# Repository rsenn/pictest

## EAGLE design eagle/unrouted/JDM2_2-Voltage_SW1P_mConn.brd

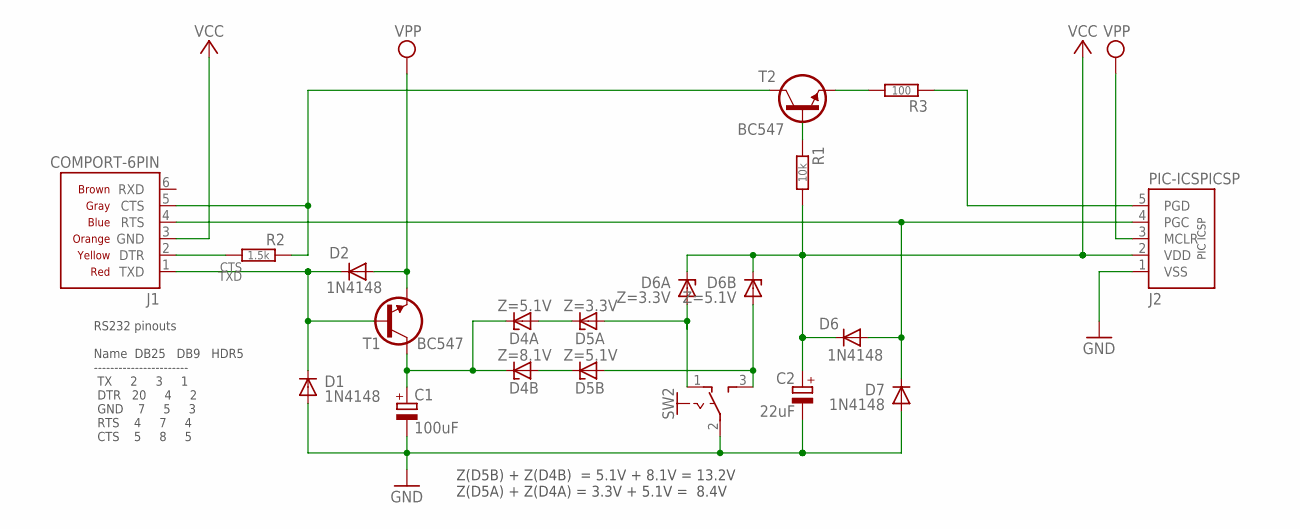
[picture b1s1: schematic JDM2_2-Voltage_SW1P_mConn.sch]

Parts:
C1: 100uF; E2,5-5
C2: 22uF; E2,5-4
D1, D2: 1N4148; DO34-5
D4A: Z=5.1V; DO34Z2,5
D4B: Z=8.1V; DO34Z2,5
D5A: Z=3.3V; DO34Z5
D5B: Z=5.1V; DO34Z5
D6: 1N4148; DO34-5V
D6A: Z=3.3V; DO34Z10V
D6B: Z=5.1V; DO34Z10V
D7: 1N4148; DO34-7V
J1: COMPORT-6PIN; RS232-6PIN
J2: PIC-ICSPICSP; PIC-ICSP
R1: 10k; 0202/7-V
R2: 1.5k; 0202/7-V
R3: 100; 0202/7
SW2: SL-SW-1P-2T-H; SLSW-1P2T-H
T1, T2: BC547; TO92-CBE

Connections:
/MCLR: D2.A, J2.3 (MCLR), T1.E
CLK: D6.A, D7.C, J1.4 (RTS), J2.4 (PGC)
CTS: J1.5 (CTS), R2.1, T2.C
DATA: R3.2, T2.E
GND: C1.-, C2.-, D1.A, D7.A, J2.1 (VSS), SW2.2
unnamed: R1.1, T2.B
unnamed: D5A.A, D6A.A, SW2.1 (O)
unnamed: D5B.A, D6B.A, SW2.3 (S)
unnamed: D4A.A, D5A.C
unnamed: J1.2 (DTR), R2.2
unnamed: D4B.A, D5B.C
PGD: J2.5 (PGD), R3.1
TXD: D1.C, D2.C, J1.1 (TXD), T1.B
VCC: C2.+, D6.C, D6A.C, D6B.C, J1.3 (GND), J2.2 (VDD), R1.2
VPP: C1.+, D4A.C, D4B.C, T1.C

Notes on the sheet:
RS232 pinouts Name DB25 DB9 HDR5 ----------------------- TX 2 3 1 DTR 20 4 2 GND 7 5 3 RTS 4 7 4 CTS 5 8 5
Z(D5B) + Z(D4B) = 5.1V + 8.1V = 13.2V Z(D5A) + Z(D4A) = 3.3V + 5.1V = 8.4V

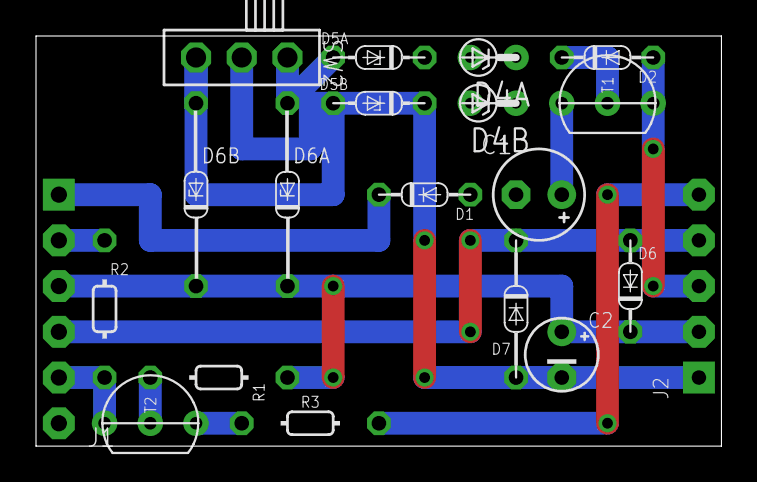
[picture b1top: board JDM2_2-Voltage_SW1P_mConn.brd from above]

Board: 2 copper layers, 38.1 x 22.8 mm, 20 parts (0 on the bottom side), 15 nets.

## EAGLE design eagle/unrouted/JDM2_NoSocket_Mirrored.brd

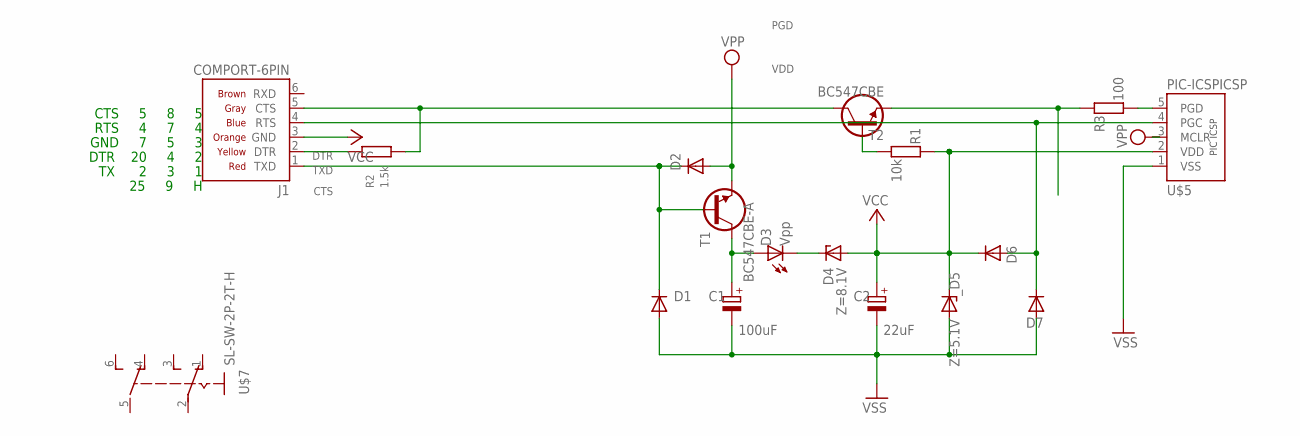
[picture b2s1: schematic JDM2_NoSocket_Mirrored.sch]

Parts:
C1: 100uF; E5-4
C2: 22uF; E2,5-4
D1: 1N4148; DO34-2,5-A
D2, D7: 1N4148; DO34-7
D3: Vpp; LED3MM
D4: Z=8.1V; DO34Z5
D6: 1N4148; DO34-5
J1: COMPORT-6PIN; RS232-6PIN
R1: 10k; 0202/5
R2: 1.5k; 0202/7
R3: 100; 0202/5
T1: BC547CBE-A; TO92-CBE-A
T2: BC547CBE; TO92-CBE
U$5: PIC-ICSPICSP; PIC-ICSP
U$7: SL-SW-2P-2T-H; SLSW-2P2T-H
_D5: Z=5.1V; DO35Z2_54

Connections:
/MCLR: D2.A, T1.E, U$5.3 (MCLR)
CLK: D6.A, D7.C, J1.4 (RTS), U$5.4 (PGC)
CTS: J1.5 (CTS), R2.2, T2.C
DATA: R3.2, T2.E
DTR: J1.2 (DTR), R2.1
unnamed: R1.1, T2.B
unnamed: D3.K (C), D4.C
PGD: R3.1, U$5.5 (PGD)
TXD: D1.C, D2.C, J1.1 (TXD), T1.B
VDD: C2.+, D4.A, D6.C, J1.3 (GND), R1.2, U$5.2 (VDD), _D5.C
VPP: C1.+, D3.A, T1.C
VSS: C1.-, C2.-, D1.A, D7.A, U$5.1 (VSS), _D5.A

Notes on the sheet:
DTR 20 4 2
TX 2 3 1
CTS 5 8 5
GND 7 5 3
RTS 4 7 4
25 9 H

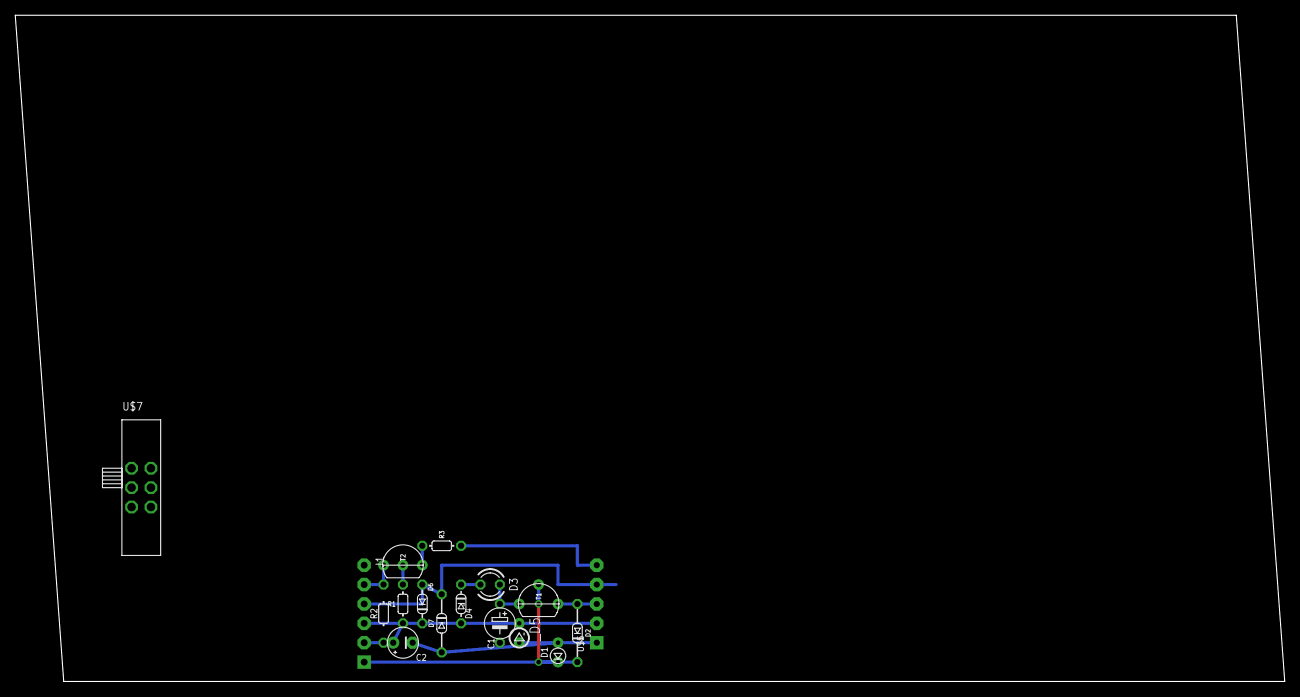
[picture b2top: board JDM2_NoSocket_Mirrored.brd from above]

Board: 2 copper layers, 166.3 x 87.3 mm, 17 parts (0 on the bottom side), 12 nets.

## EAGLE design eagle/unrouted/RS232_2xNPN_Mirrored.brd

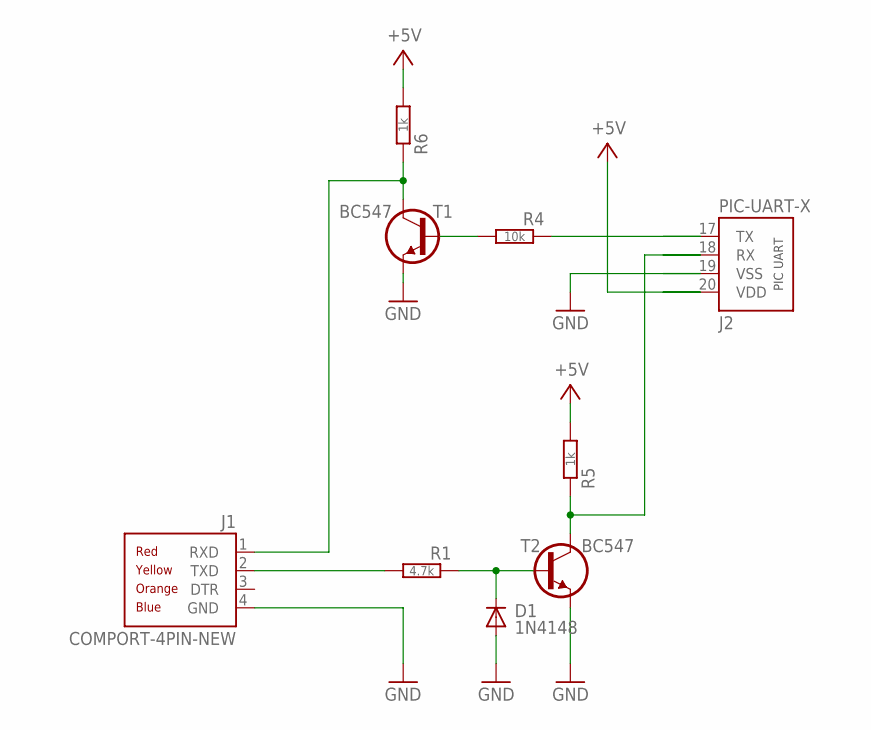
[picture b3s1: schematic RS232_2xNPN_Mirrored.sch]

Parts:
D1: 1N4148; DO34-5
J1: COMPORT-4PIN-NEW; RS232-4PIN-NEW
J2: PIC-UART-X
R1: 4.7k; 0202/7
R4: 10k; 0202/7
R5: 1k; 0202/7-V
R6: 1k; 0202/7
T1, T2: BC547; TO92-CBE

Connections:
+5V: J2.20 (VDD), R5.2, R6.2
GND: D1.A, J1.4 (GND), J2.19 (VSS), T1.E, T2.E
unnamed: J2.18 (RX), R5.1, T2.C
unnamed: D1.C, R1.1, T2.B
unnamed: J1.2 (TXD), R1.2
unnamed: J2.17 (TX), R4.1
unnamed: R4.2, T1.B
unnamed: J1.1 (RXD), R6.1, T1.C

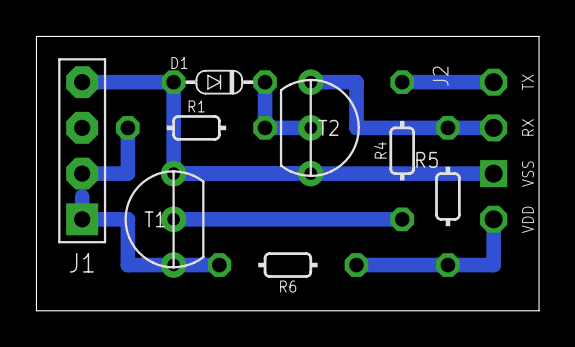
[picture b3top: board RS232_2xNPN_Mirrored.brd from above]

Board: 2 copper layers, 27.9 x 15.2 mm, 9 parts (0 on the bottom side), 8 nets.

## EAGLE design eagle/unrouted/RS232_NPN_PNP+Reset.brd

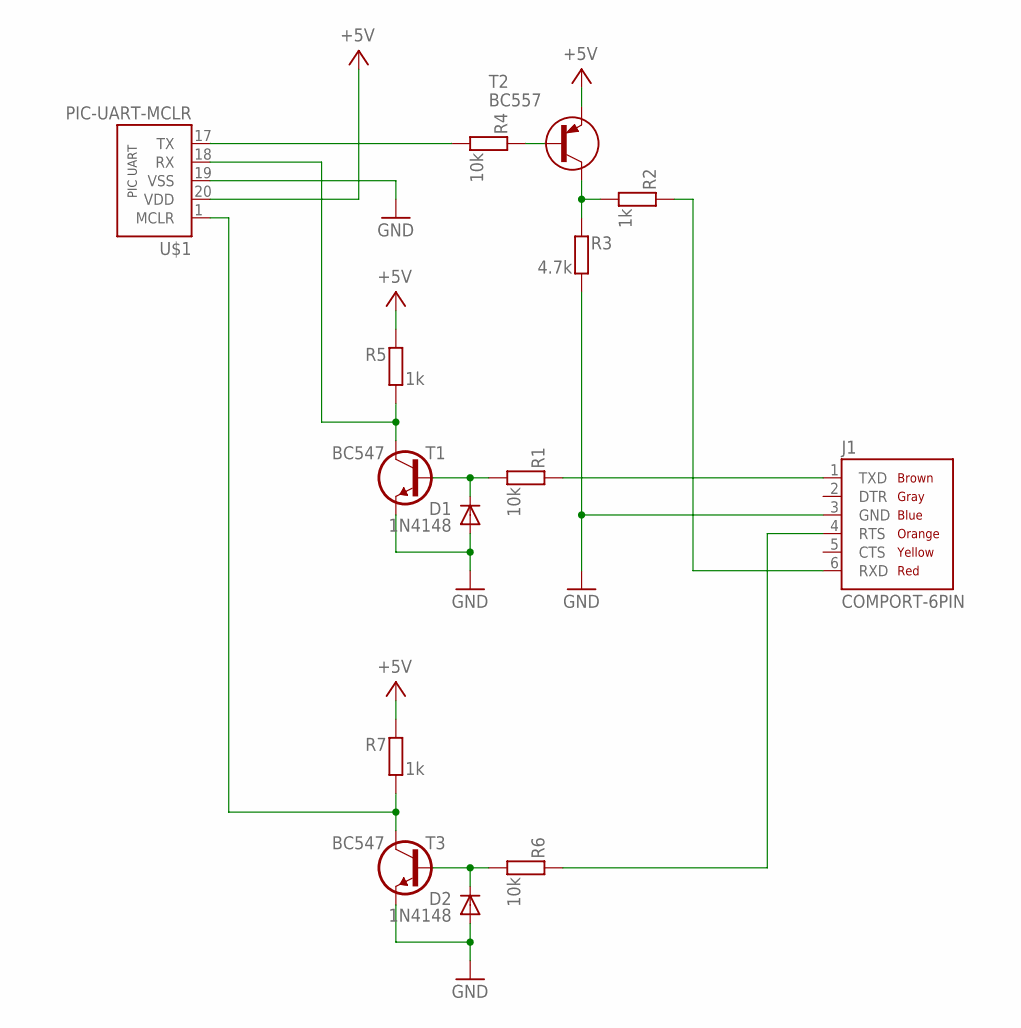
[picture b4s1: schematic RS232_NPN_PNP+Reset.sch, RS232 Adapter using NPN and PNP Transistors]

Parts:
D1, D2: 1N4148; DO34-5
J1: COMPORT-6PIN; RS232-6PIN
R1, R4, R6: 10k; 0202/5
R2, R5: 1k; 0202/5
R3: 4.7k; 0202/5
R7: 1k; 0202/2V
T1, T3: BC547; TO92-CBE
T2: BC557; TO92-CBE
U$1: PIC-UART-MCLR

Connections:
+5V: R5.2, R7.2, T2.E, U$1.20 (VDD)
GND: D1.A, D2.A, J1.3 (GND), R3.1, T1.E, T3.E, U$1.19 (VSS)
unnamed: R5.1, T1.C, U$1.18 (RX)
unnamed: D1.C, R1.1, T1.B
unnamed: J1.1 (TXD), R1.2
unnamed: R4.1, U$1.17 (TX)
unnamed: R4.2, T2.B
unnamed: R2.1, R3.2, T2.C
unnamed: J1.6 (RXD), R2.2
unnamed: R7.1, T3.C, U$1.1 (MCLR)
unnamed: D2.C, R6.1, T3.B
unnamed: J1.4 (RTS), R6.2

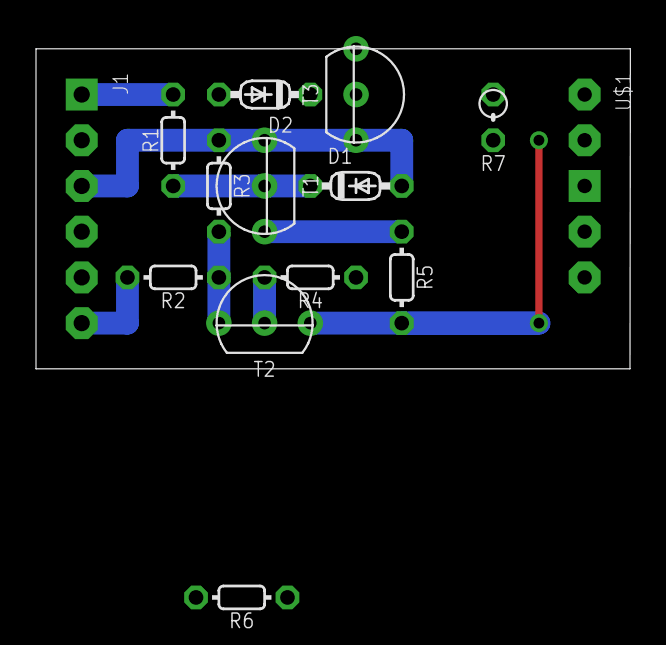
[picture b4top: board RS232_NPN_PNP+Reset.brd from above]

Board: 2 copper layers, 33.0 x 17.8 mm, 14 parts (0 on the bottom side), 12 nets.

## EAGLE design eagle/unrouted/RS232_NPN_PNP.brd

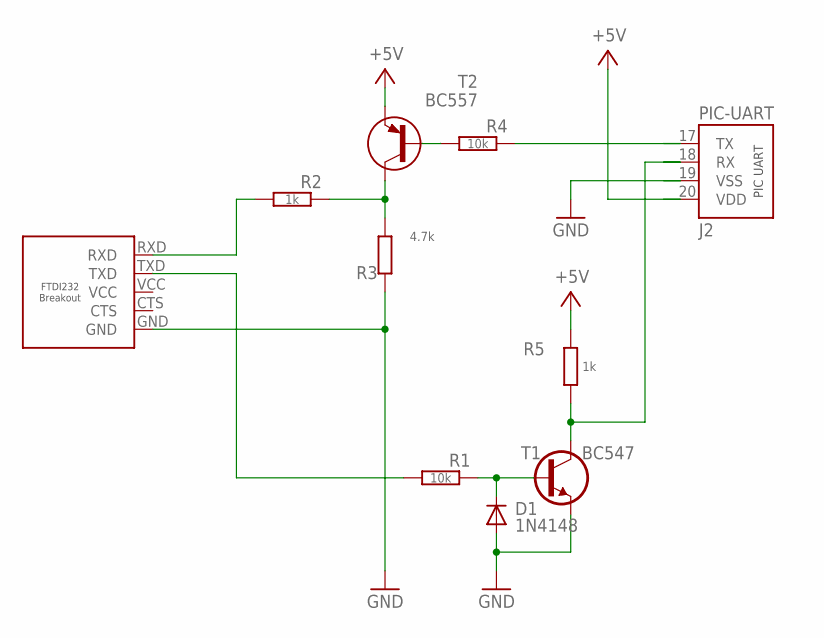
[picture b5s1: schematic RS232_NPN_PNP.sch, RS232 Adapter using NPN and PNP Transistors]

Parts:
D1: 1N4148; DO34-5
J1: FTDI232; FTDI232-BO-5-L
J2: PIC-UART
R1: 10k; 0202/5-V
R2, R5: 1k; 0202/5-V
R3: 4.7k; 0202/5-V
R4: 10k; 0202/5
T1: BC547; TO92-CBE
T2: BC557; TO92-CBE

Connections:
+5V: J2.20 (VDD), R5.2, T2.E
GND: D1.A, J1.GND, J2.19 (VSS), R3.1, T1.E
unnamed: J2.18 (RX), R5.1, T1.C
unnamed: D1.C, R1.1, T1.B
unnamed: J1.TXD, R1.2
unnamed: J2.17 (TX), R4.1
unnamed: R4.2, T2.B
unnamed: R2.1, R3.2, T2.C
unnamed: J1.RXD, R2.2

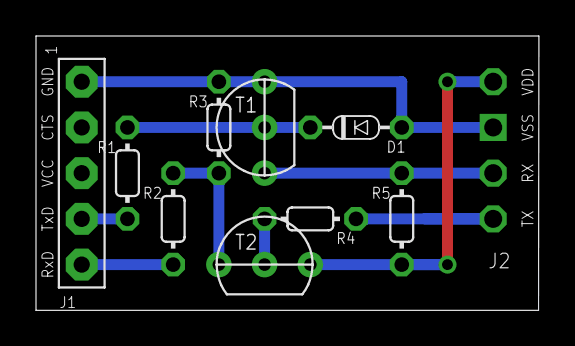
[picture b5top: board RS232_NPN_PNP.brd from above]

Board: 2 copper layers, 27.9 x 15.2 mm, 10 parts (0 on the bottom side), 9 nets.
